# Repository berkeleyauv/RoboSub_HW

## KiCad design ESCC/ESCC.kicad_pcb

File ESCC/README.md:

# ESCC

Based on the STM32F072 NOGGIN, controls a Blue Robotics ESC using PWM over CAN.

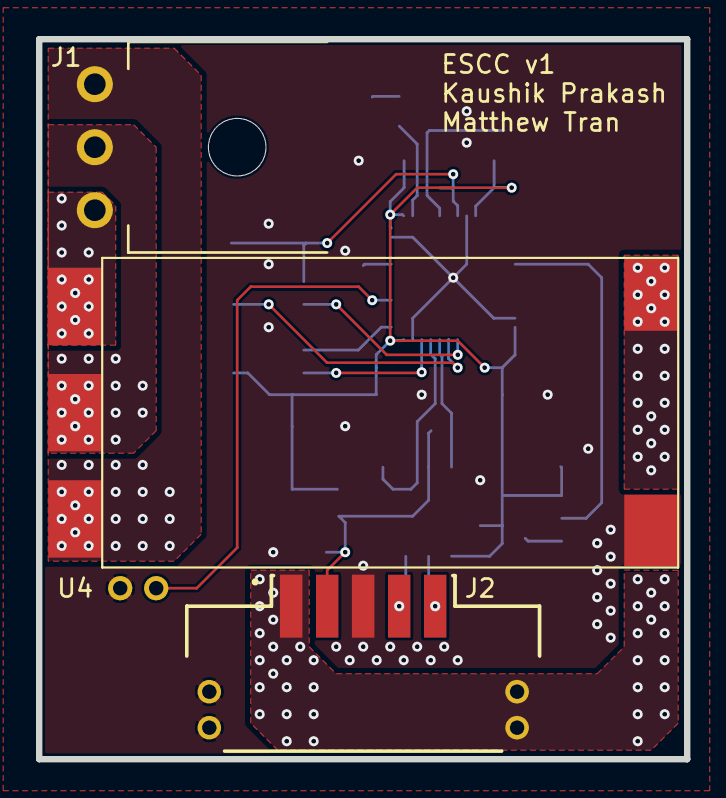
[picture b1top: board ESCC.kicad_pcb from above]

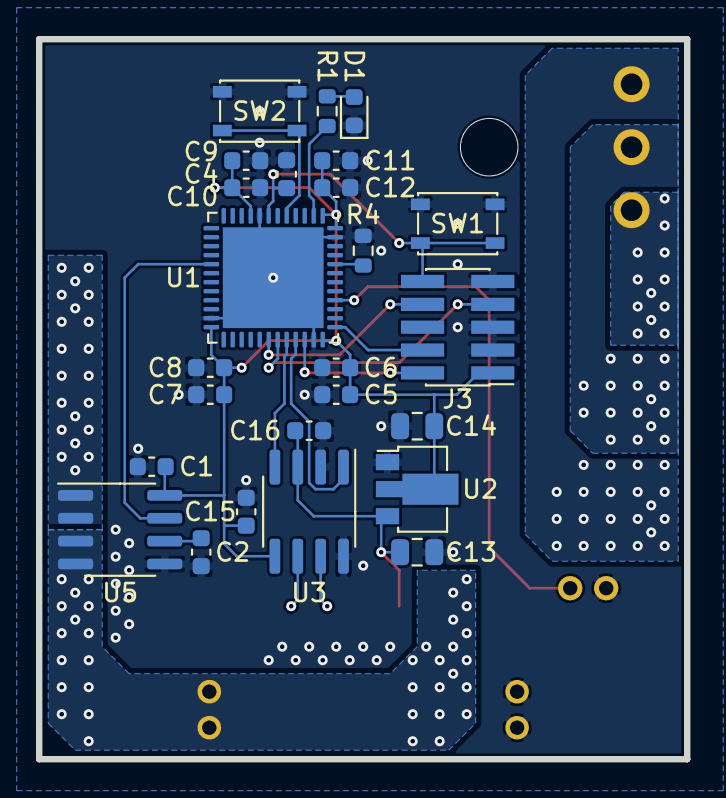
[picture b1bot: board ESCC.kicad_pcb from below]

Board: 2 copper layers, 36.0 x 40.0 mm, 28 parts (25 on the bottom side), 24 nets.

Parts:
C1, C4, C6, C8, C10, C12, C15, C16: 100n; C_0603_1608Metric
C2: DNP; C_0603_1608Metric
C5, C7, C9, C11: 1u; C_0603_1608Metric
C13, C14: 10u; C_0805_2012Metric
D1: LED; LED_0603_1608Metric
J1: Conn_01x03; Molex_UltraFit_RH_3pin
J2: Conn_01x05; Samtec_mPOWER_UMPT_RA_5pin
J3: SWD_UART; PinHeader_2x05_P1.27mm_Vertical_SMD
R1: 150; R_0603_1608Metric
R4: 100k; R_0603_1608Metric
SW1: RST; SW_SPST_PTS810
SW2: DBG; SW_SPST_PTS810
U1: STM32F072CBUx; QFN-48-1EP_7x7mm_P0.5mm_EP5.6x5.6mm
U2: AZ1117-3.3; SOT-89-3
U3: ATA6561; SOIC-8_3.9x4.9mm_P1.27mm
U4: BESC
U5: ACS725xLCTR-30AB; SOIC-8_3.9x4.9mm_P1.27mm

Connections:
+3V3: C1.2, C5.1, C6.1, C7.1, C8.1, C9.1, C10.1, C11.1, C12.1, C14.1, C15.1, J3.1, U1.1, U1.9, U1.24, U1.36, U1.48, U2.2, U3.5, U5.8
+5V: C13.1, C16.1, J2.2, U2.3, U3.3
+12V: J2.1, U5.3, U5.4
/12V_SENSED: U4.4, U5.1, U5.2
/CAN/CANH: J2.4, U3.7
/CAN/CANL: J2.5, U3.6
/CAN_RX: U1.32, U3.4
/CAN_TX: U1.33, U3.1
/CURR_OUT: U1.17, U5.7
/DBG: SW2.1, U1.5
/ESC_SIG: U1.40, U4.2
/LED: R1.2, U1.2
/NOGGIN/PA9(UART_TX): J3.8, U1.30
/NOGGIN/PA10(UART_RX): J3.7, U1.31
/NOGGIN/SWCLK: J3.4, U1.37
/NOGGIN/SWDIO: J3.2, U1.34
/RST: C4.1, J3.10, SW1.1, U1.7
GND: C1.1, C2.1, C4.2, C5.2, C6.2, C7.2, C8.2, C9.2, C10.2, C11.2, C12.2, C13.2, C14.2, C15.2, C16.2, D1.1, J2.3, J3.3, J3.5, J3.9, R4.2, SW1.2, SW2.2, U1.8, U1.23, U1.35, U1.47, U1.49, U2.1, U3.2, U3.8, U4.1, U4.3, U5.5
unnamed: C2.2, U5.6
unnamed: D1.2, R1.1
unnamed: J1.1, U4.7
unnamed: J1.2, U4.6
unnamed: J1.3, U4.5
unnamed: R4.1, U1.44

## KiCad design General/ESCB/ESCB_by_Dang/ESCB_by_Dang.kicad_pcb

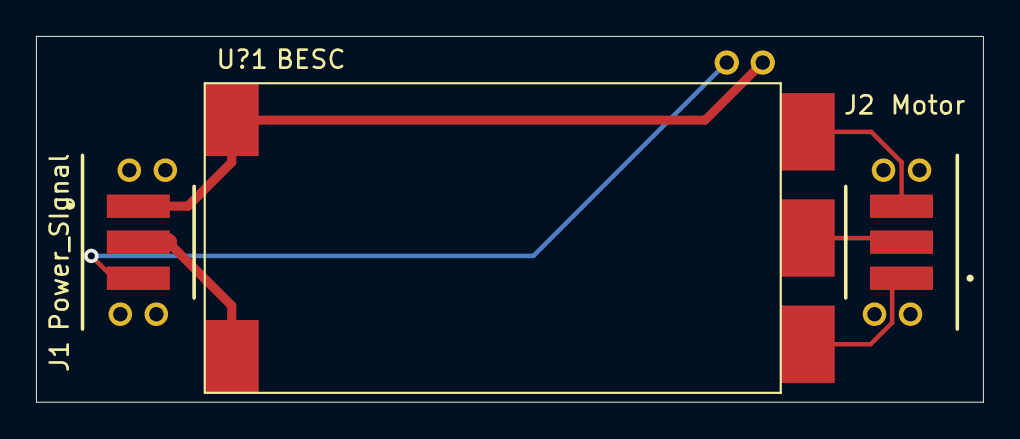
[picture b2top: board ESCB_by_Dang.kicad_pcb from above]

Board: 2 copper layers, 52.6 x 20.3 mm, 3 parts (0 on the bottom side), 6 nets.

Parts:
J1: Power_Signal; Samtec_mPOWER_UMPS_3pin
J2: Motor; Samtec_mPOWER_UMPS_3pin
U?1: BESC

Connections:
GND: J1.1, U?1.1, U?1.3
unnamed: J1.3, U?1.2
unnamed: J2.1, U?1.5
unnamed: J2.2, U?1.6
unnamed: J2.3, U?1.7
VCC: J1.2, U?1.4

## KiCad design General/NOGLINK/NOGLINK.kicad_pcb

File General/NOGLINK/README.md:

# NOGLINK

Carrier for STLINK-V3MODS with CAN transceiver, button, RGB LED, SWD, UART, and stbridge breakout.

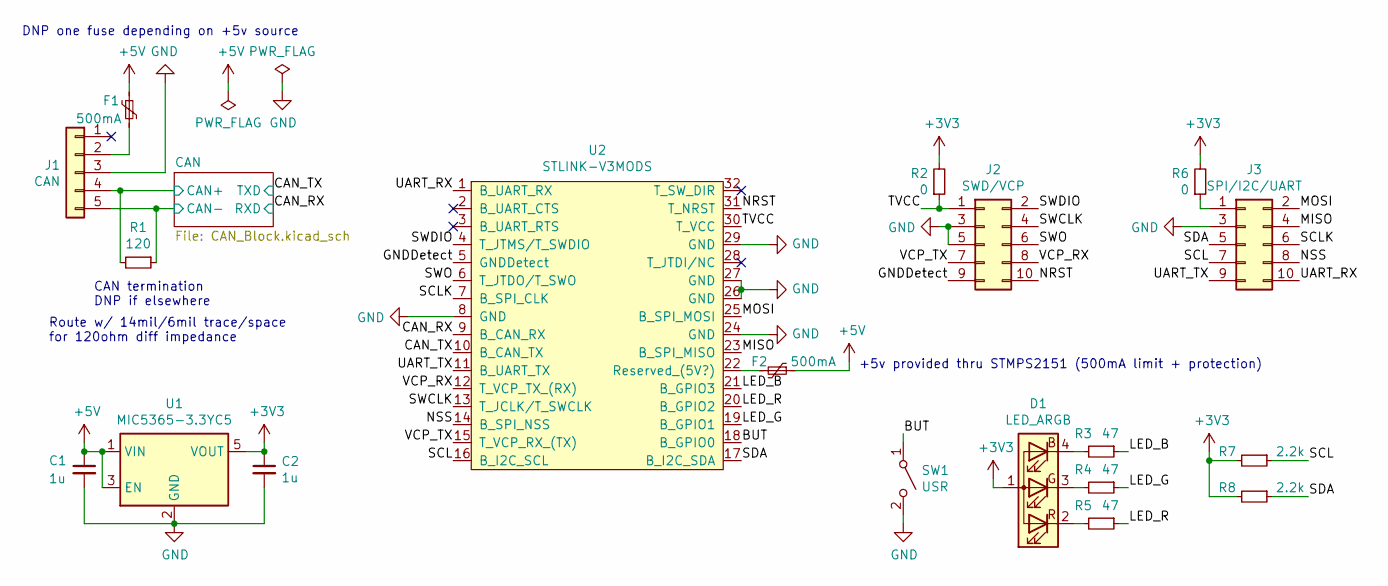
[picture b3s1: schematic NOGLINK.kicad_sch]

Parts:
C1, C2: 1u; C_0603_1608Metric
D1: LED_ARGB; LED_Cree-PLCC4_2x2mm_CW
F1, F2: 500mA; Fuse_1206_3216Metric
J1: CAN; Molex_DuraClik_RH_5pin
J2: SWD/VCP; PinHeader_2x05_P1.27mm_Vertical_SMD
J3: SPI/I2C/UART; PinHeader_2x05_P1.27mm_Vertical_SMD
R1: 120; R_0603_1608Metric
R2, R6: 0; R_0603_1608Metric
R3, R4, R5: 47; R_0603_1608Metric
R7, R8: 2.2k; R_0603_1608Metric
SW1: USR; SW_SPST_PTS810
U1: MIC5365-3.3YC5; SOT-353_SC-70-5
U2: STLINK-V3MODS

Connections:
+3V3: C2.1, D1.1 (A), R2.2, R6.2, R7.2, R8.2, U1.5 (VOUT); also elsewhere on the board
+5V: C1.1, F1.1, F2.1, U1.1 (VIN), U1.3 (EN); also elsewhere on the board
/BUT: SW1.1 (A), U2.18 (B_GPIO0)
/CAN/CAN+: J1.4, R1.2; also elsewhere on the board
/CAN/CAN-: J1.5, R1.1; also elsewhere on the board
/CAN_RX: U2.9 (B_CAN_RX); also elsewhere on the board
/CAN_TX: U2.10 (B_CAN_TX); also elsewhere on the board
/GNDDetect: J2.9, U2.5 (GNDDetect)
/LED_B: R3.1, U2.21 (B_GPIO3)
/LED_G: R4.1, U2.19 (B_GPIO1)
/LED_R: R5.1, U2.20 (B_GPIO2)
/MISO: J3.4, U2.23 (B_SPI_MISO)
/MOSI: J3.2, U2.25 (B_SPI_MOSI)
/NRST: J2.10, U2.31 (T_NRST)
/NSS: J3.8, U2.14 (B_SPI_NSS)
/SCL: J3.7, R7.1, U2.16 (B_I2C_SCL)
/SCLK: J3.6, U2.7 (B_SPI_CLK)
/SDA: J3.5, R8.1, U2.17 (B_I2C_SDA)
/SWCLK: J2.4, U2.13 (T_JCLK/T_SWCLK)
/SWDIO: J2.2, U2.4 (T_JTMS/T_SWDIO)
/SWO: J2.6, U2.6 (T_JTDO/T_SWO)
/TVCC: J2.1, R2.1, U2.30 (T_VCC)
/UART_RX: J3.10, U2.1 (B_UART_RX)
/UART_TX: J3.9, U2.11 (B_UART_TX)
/VCP_RX: J2.8, U2.12 (T_VCP_TX_(RX))
/VCP_TX: J2.7, U2.15 (T_VCP_RX_(TX))
GND: C1.2, C2.2, J1.3, J1.MP, J2.3, J2.5, J3.3, SW1.2 (B), U1.2 (GND), U2.8 (GND), U2.24 (GND), U2.26 (GND), U2.27 (GND), U2.29 (GND); also elsewhere on the board
unnamed: D1.2 (RK), R5.2
unnamed: D1.3 (GK), R4.2
unnamed: D1.4 (BK), R3.2
unnamed: F1.2, J1.2
unnamed: F2.2, U2.22 (Reserved_(5V?))
unnamed: J3.1, R6.1

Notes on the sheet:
+5v provided thru STMPS2151 (500mA limit + protection)
DNP one fuse depending on +5v source
Route w/ 14mil/6mil trace/space for 120ohm diff impedance
CAN termination DNP if elsewhere

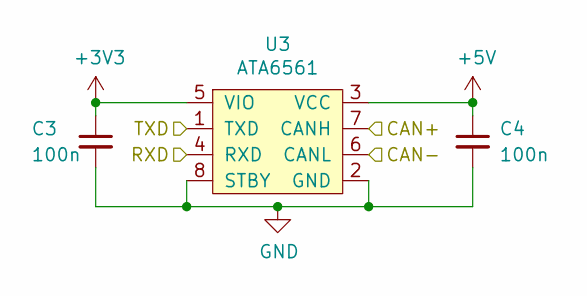
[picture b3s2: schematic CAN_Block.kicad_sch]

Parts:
C3, C4: 100n; C_0603_1608Metric
U3: ATA6561; SOIC-8_3.9x4.9mm_P1.27mm

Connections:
+3V3: C3.1, U3.5 (VIO); also elsewhere on the board
+5V: C4.1, U3.3 (VCC); also elsewhere on the board
/CAN/CAN+: U3.7 (CANH); also elsewhere on the board
/CAN/CAN-: U3.6 (CANL); also elsewhere on the board
/CAN_RX: U3.4 (RXD); also elsewhere on the board
/CAN_TX: U3.1 (TXD); also elsewhere on the board
GND: C3.2, C4.2, U3.2 (GND), U3.8 (STBY); also elsewhere on the board

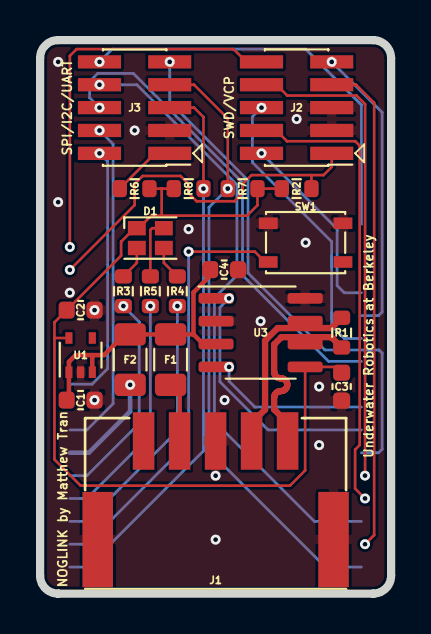
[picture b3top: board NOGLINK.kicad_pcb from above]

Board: 2 copper layers, 19.5 x 30.8 mm, 22 parts (1 on the bottom side), 33 nets.

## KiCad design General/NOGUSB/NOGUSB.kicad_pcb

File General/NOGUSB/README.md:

# NOGUSB

Board for testing various capabilities of the STM32G0B1 including USB-C PD, USB, bootloaders, and FDCAN. Intended as potential replacement for NOGLINK.

If using the bootloader to program, make sure to unset the nBOOT_SEL before first flash or you will lose access to the bootloader.

## Revisions

### v1.1

- Added connections for DBCC pins, fixing no power on startup
- Rerouted UART pins to a different pair

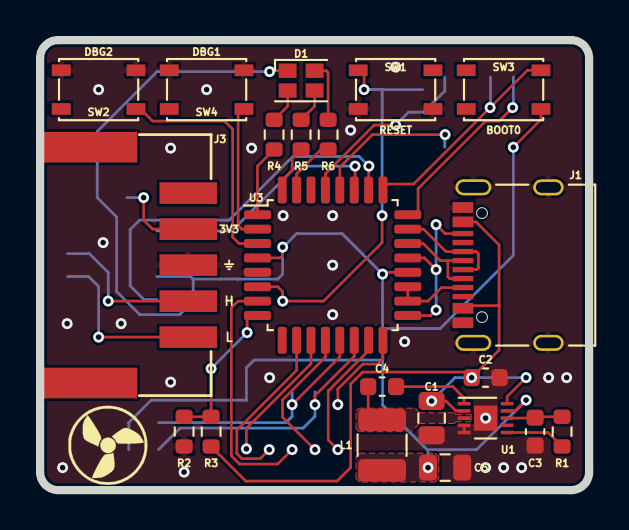
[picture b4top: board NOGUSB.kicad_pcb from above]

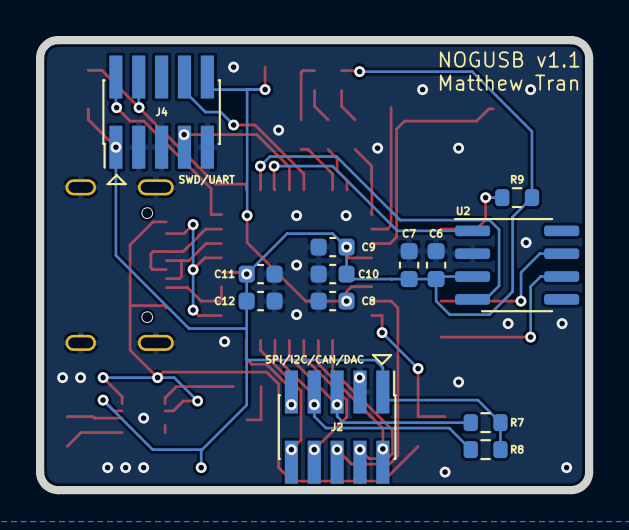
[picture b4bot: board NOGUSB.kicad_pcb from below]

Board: 2 copper layers, 30.5 x 25.0 mm, 35 parts (13 on the bottom side), 38 nets.

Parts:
C1, C5: 22u; C_0805_2012Metric
C2, C4, C6, C8, C9, C11: 100n; C_0603_1608Metric
C3: 1u; C_0603_1608Metric
C7, C10, C12: 4.7u; C_0603_1608Metric
D1: LED_ARGB; LED_Cree-PLCC4_2x2mm_CW
H1: Logo; auv_logo
J1: USB4105-GF-A; USB_C_Receptacle_Palconn_UTC16-G
J2: SPI/I2C/CAN/DAC; PinHeader_2x05_P1.27mm_Vertical_SMD
J3: CAN; Molex_DuraClik_RH_5pin
J4: SWD_UART; PinHeader_2x05_P1.27mm_Vertical_SMD
L1: 10u; L_1210_3225Metric
R1, R2: 100k; R_0603_1608Metric
R3: 10k; R_0603_1608Metric
R4, R5, R6: 47; R_0603_1608Metric
R7, R8: 2k2; R_0603_1608Metric
R9: 0; R_0603_1608Metric
SW1: RST; SW_SPST_PTS810
SW2: DBG2; SW_SPST_PTS810
SW3: BOOT0; SW_SPST_PTS810
SW4: DBG1; SW_SPST_PTS810
U1: MAX77596ETBB+
U2: TCAN330G; SOIC-8_3.9x4.9mm_P1.27mm
U3: STM32G0B1KxTxN; LQFP-32_7x7mm_P0.8mm

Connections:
+3V3: C5.1, C6.1, C7.1, C9.1, C10.1, C11.1, C12.1, D1.1, J2.1, J4.1, L1.2, R7.2, R8.2, R9.1, SW3.2, U1.9, U2.3, U3.4, U3.20
/BOOT0: J4.4, SW3.1, U3.25
/CAN2_RX: J2.10, U3.15
/CAN2_TX: J2.9, U3.16
/CAN/CANH: J3.4, U2.7
/CAN/CANL: J3.5, U2.6
/CAN_RX: U2.4, U3.26
/CAN_TX: U2.1, U3.27
/DAC: J2.8, U3.12
/DBG1: SW4.1, U3.2
/DBG2: SW2.1, U3.3
/I2C_SCL: J2.7, R8.1, U3.14
/I2C_SDA: J2.5, R7.1, U3.13
/LED_B: R4.1, U3.1
/LED_G: R5.1, U3.32
/LED_R: R6.1, U3.31
/NOGGIN/PA13(SWDIO): J4.2, U3.24
/NOGGIN/PD2: J4.7, U3.28
/NOGGIN/PD3: J4.8, U3.29
/RST: C8.1, J4.10, SW1.1, U3.6
/SPI_CLK: J2.6, U3.7
/SPI_MISO: J2.4, U3.10
/SPI_MOSI: J2.2, U3.11
/USB_CC1: J1.A5, U3.18, U3.19
/USB_CC2: J1.B5, U3.17, U3.21
/USB_DM: J1.A7, J1.B7, U3.22
/USB_DP: J1.A6, J1.B6, U3.23
/VBUS_MON: R2.2, R3.1, U3.8
GND: C1.2, C2.2, C3.2, C5.2, C6.2, C7.2, C8.2, C9.2, C10.2, C11.2, C12.2, J1.A1, J1.A12, J1.B1, J1.B12, J1.S1, J2.3, J3.3, J4.3, J4.5, J4.9, R3.2, SW1.2, SW2.2, SW4.2, U1.4, U1.5, U1.11, U2.2, U3.5
unnamed: C3.1, R1.1, U1.8
unnamed: C4.1, L1.1, U1.3
unnamed: C4.2, U1.1
unnamed: D1.2, R6.2
unnamed: D1.3, R5.2
unnamed: D1.4, R4.2
unnamed: J3.2, R9.2
unnamed: R1.2, U1.6
VBUS: C1.1, C2.1, J1.A4, J1.A9, J1.B4, J1.B9, R2.1, U1.2, U1.10

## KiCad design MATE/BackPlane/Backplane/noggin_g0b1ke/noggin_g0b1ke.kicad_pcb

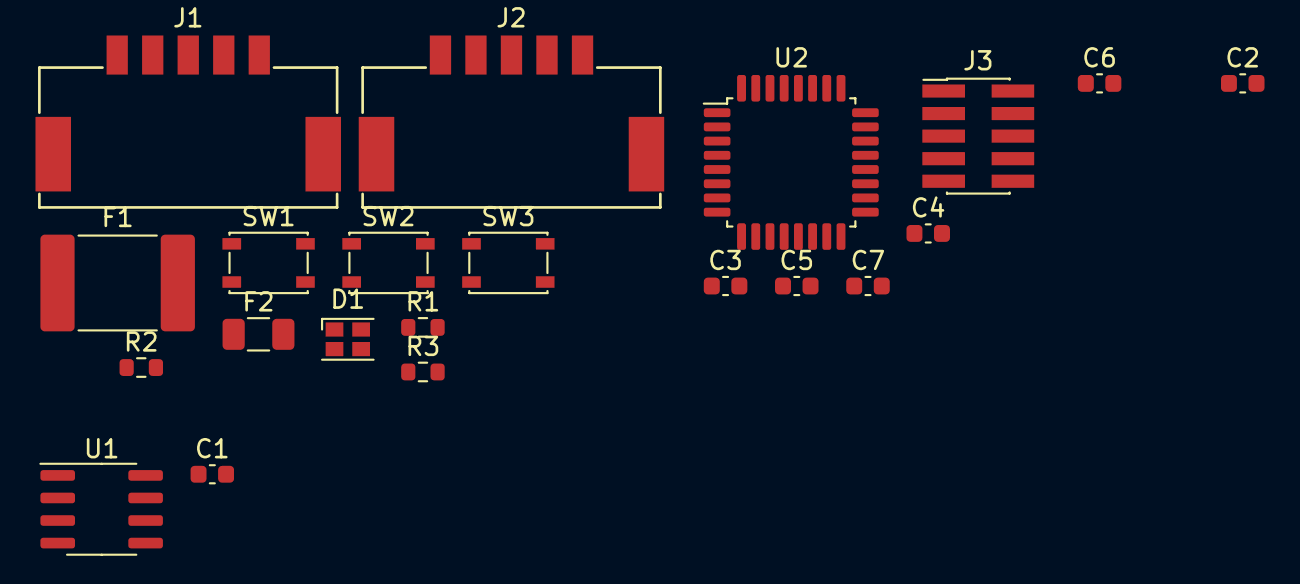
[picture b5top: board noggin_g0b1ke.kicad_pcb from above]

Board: 2 copper layers, 21 parts (0 on the bottom side), 21 nets, no tracks yet.

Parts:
C1, C3, C4, C6: 100n; C_0603_1608Metric
C2, C5, C7: 4.7u; C_0603_1608Metric
D1: LED_ARGB; LED_Cree-PLCC4_2x2mm_CW
F1: 5A; Fuse_2920_7451Metric
F2: 1A; Fuse_1206_3216Metric
J1, J2: CAN; Molex_DuraClik_Vert_5pin
J3: SWD_UART; PinHeader_2x05_P1.27mm_Vertical_SMD
R1, R2, R3: 47; R_0603_1608Metric
SW1: DBG2; SW_SPST_PTS810
SW2: DBG1; SW_SPST_PTS810
SW3: RST; SW_SPST_PTS810
U1: TCAN330G; SOIC-8_3.9x4.9mm_P1.27mm
U2: STM32G0B1KxTxN; LQFP-32_7x7mm_P0.8mm

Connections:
+3V3: C1.1, C2.1, C4.1, C5.1, C6.1, C7.1, D1.1, F2.1, J3.1, U1.3, U2.4, U2.20
/CAN/CANH: J1.4, J2.4, U1.7
/CAN/CANL: J1.5, J2.5, U1.6
/CAN_RX: U1.4, U2.26
/CAN_TX: U1.1, U2.27
/DBG1: SW2.1, U2.2
/DBG2: SW1.1, U2.3
/LED_B: R1.1, U2.1
/LED_G: R2.1, U2.32
/LED_R: R3.1, U2.31
/NOGGIN/PA9(TX): J3.8, U2.19
/NOGGIN/PA10(RX): J3.7, U2.21
/NOGGIN/PA13(SWDIO): J3.2, U2.24
/NOGGIN/PA14-BOOT0(SWCLK): J3.4, U2.25
/RST: C3.1, J3.10, SW3.1, U2.6
GND: C1.2, C2.2, C3.2, C4.2, C5.2, C6.2, C7.2, J1.3, J2.3, J3.3, J3.5, J3.9, SW1.2, SW2.2, SW3.2, U1.2, U2.5
unnamed: D1.2, R3.2
unnamed: D1.3, R2.2
unnamed: D1.4, R1.2
unnamed: F1.2, J1.1, J2.1
unnamed: F2.2, J1.2, J2.2

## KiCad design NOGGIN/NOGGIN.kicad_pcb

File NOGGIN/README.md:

# NOGGIN

Based on the STM32F072 (or alternately the STM32F091), NOGGIN is a general purpose board containing current/voltage sense, brushed motor driver, CAN, I2C/UART/DAC/ADC connectors, debug switches, RGB LED, and GPIO breakout.

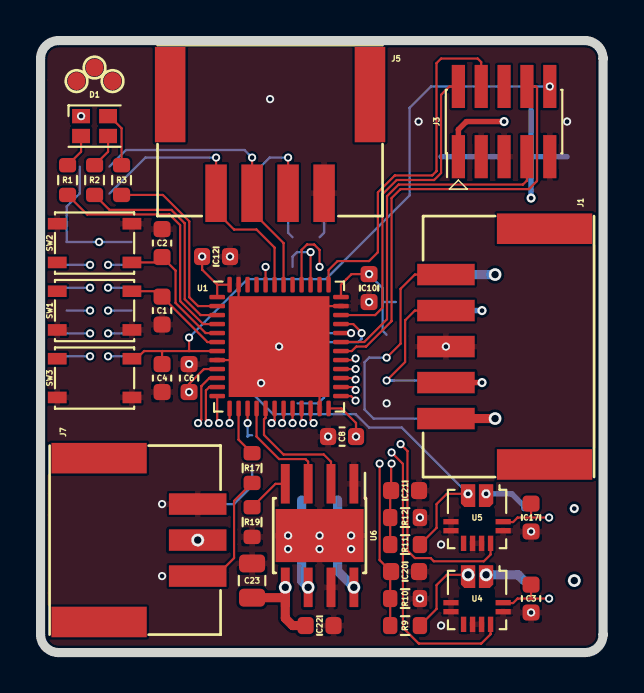
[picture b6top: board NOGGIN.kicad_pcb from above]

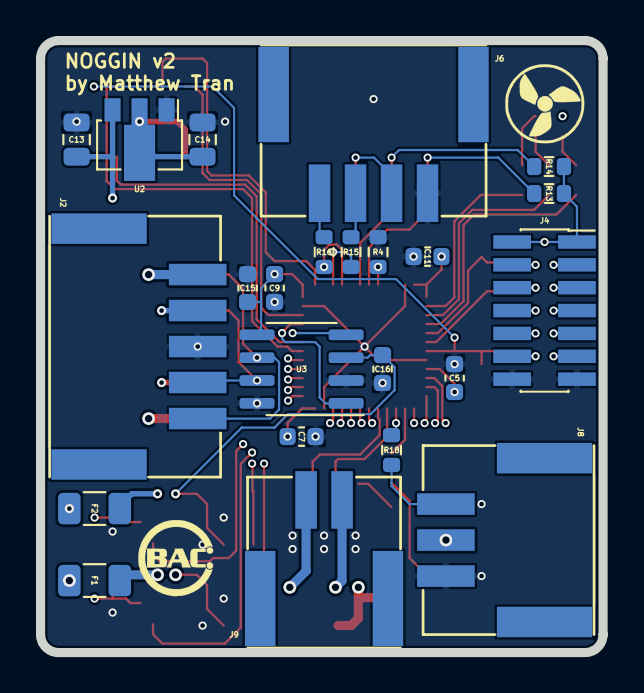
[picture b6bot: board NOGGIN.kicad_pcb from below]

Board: 4 copper layers, 31.2 x 34.0 mm, 58 parts (23 on the bottom side), 55 nets.

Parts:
 : version_dots
C1, C2, C3, C4, C6, C8, C10, C12, C15, C16, C17, C20, C21, C22: 100n; C_0603_1608Metric
C5, C7, C9, C11: 1u; C_0603_1608Metric
C13, C14, C23: 10u; C_0805_2012Metric
D1: LED_ARGB; LED_Cree-PLCC4_2x2mm_CW
F1: 5A; Fuse_1206_3216Metric
F2: 1A; Fuse_1206_3216Metric
J1, J2: CAN; Molex_DuraClik_RH_5pin
J3: SWD_UART; PinHeader_2x05_P1.27mm_Vertical_SMD
J4: Extra; PinSocket_2x07_P1.27mm_Vertical_SMD
J5: I2C; Molex_DuraClik_RH_4pin
J6: UART; Molex_DuraClik_RH_4pin
J7: DAC1; Molex_DuraClik_RH_3pin
J8: DAC2; Molex_DuraClik_RH_3pin
J9: MOTOR; Molex_DuraClik_RH_2pin
R1, R2, R3: 47; R_0603_1608Metric
R4, R9: 100k; R_0603_1608Metric
R10, R12: 10k; R_0603_1608Metric
R11: 47k; R_0603_1608Metric
R13, R14: 2.2k; R_0603_1608Metric
R15, R16, R17, R18: 22; R_0603_1608Metric
R19: 22k; R_0603_1608Metric
SW1: DBG2; SW_SPST_PTS810
SW2: DBG1; SW_SPST_PTS810
SW3: RST; SW_SPST_PTS810
U1: STM32F072CBUx; QFN-48-1EP_7x7mm_P0.5mm_EP5.6x5.6mm
U2: AZ1117-3.3; SOT-89-3
U3: ATA6561; SOIC-8_3.9x4.9mm_P1.27mm
U4, U5: ACS70331; Allegro_QFN-12-10-1EP_3x3mm_P0.5mm
U6: DRV8871DDA; Texas_HTSOP-8-1EP_3.9x4.9mm_P1.27mm_EP2.95x4.9mm_Mask2.4x3.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

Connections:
+3V3: C3.1, C5.1, C6.1, C7.1, C8.1, C9.1, C10.1, C11.1, C12.1, C14.1, C15.1, C17.1, D1.1, J3.1, J4.1, J4.2, J5.2, J6.2, R13.1, R14.1, U1.1, U1.9, U1.24, U1.36, U1.48, U2.2, U3.5, U4.10, U5.10
+5V: C13.1, C16.1, R11.1, U2.3, U3.3, U5.2
+12V: C22.1, C23.1, J7.2, J8.2, R9.1, U4.2, U6.5
/5v_Isens: U1.13, U5.8
/5v_Sens+: F2.1, U5.1
/5v_Vsens: C21.2, R11.2, R12.1, U1.11
/12v_Isens: U1.12, U4.8
/12v_Sens+: F1.1, U4.1
/12v_Vsens: C20.2, R9.2, R10.1, U1.10
/CAN/CANH: J1.4, J2.4, U3.7
/CAN/CANL: J1.5, J2.5, U3.6
/CAN_RX: U1.32, U3.4
/CAN_TX: U1.33, U3.1
/DAC1: R17.2, U1.14
/DAC2: R18.2, U1.15
/DBG1: C2.1, SW2.1, U1.5
/DBG2: C1.1, SW1.1, U1.6
/LED_B: R1.1, U1.4
/LED_G: R2.1, U1.3
/LED_R: R3.1, U1.2
/NOGGIN/PA9(UART_TX): J3.8, U1.30
/NOGGIN/PA10(UART_RX): J3.7, U1.31
/NOGGIN/SWCLK: J3.4, U1.37
/NOGGIN/SWDIO: J3.2, U1.34
/PA8: J4.3, U1.29
/PB0: J4.12, U1.18
/PB1: J4.11, U1.19
/PB2: J4.10, U1.20
/PB10: J4.9, U1.21
/PB11: J4.8, U1.22
/PB12: J4.7, U1.25
/PB13: J4.6, U1.26
/PB14: J4.5, U1.27
/PB15: J4.4, U1.28
/RST: C4.1, J3.10, SW3.1, U1.7
/RX: R16.2, U1.40
/SCL: J5.3, R14.2, U1.42
/SDA: J5.4, R13.2, U1.43
/TX: R15.2, U1.39
/motor_in1: U1.16, U6.3
/motor_in2: U1.17, U6.2
GND: C1.2, C2.2, C3.2, C4.2, C5.2, C6.2, C7.2, C8.2, C9.2, C10.2, C11.2, C12.2, C13.2, C14.2, C15.2, C16.2, C17.2, C20.1, C21.1, C22.2, C23.2, J1.3, J2.3, J3.3, J3.5, J3.9, J4.13, J4.14, J5.1, J6.1, J7.1, J8.1, R4.2, R10.2, R12.2, R19.2, SW1.2, SW2.2, SW3.2, U1.8, U1.23, U1.35, U1.47, U1.49, U2.1, U3.2, U3.8, U4.3, U4.4, U4.6, U4.7, U4.9, U5.3, U5.4, U5.6, U5.7, U5.9, U6.1, U6.7, U6.9
unnamed: D1.2, R3.2
unnamed: D1.3, R2.2
unnamed: D1.4, R1.2
unnamed: F1.2, J1.1, J2.1
unnamed: F2.2, J1.2, J2.2
unnamed: J6.3, R15.1
unnamed: J6.4, R16.1
unnamed: J7.3, R17.1
unnamed: J8.3, R18.1
unnamed: J9.1, U6.8
unnamed: J9.2, U6.6
unnamed: R4.1, U1.44
unnamed: R19.1, U6.4

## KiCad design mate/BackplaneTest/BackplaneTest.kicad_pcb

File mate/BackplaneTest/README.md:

# BackplaneTest

Tests the ESCC and PCC along with a Molex Super Sabre for power.

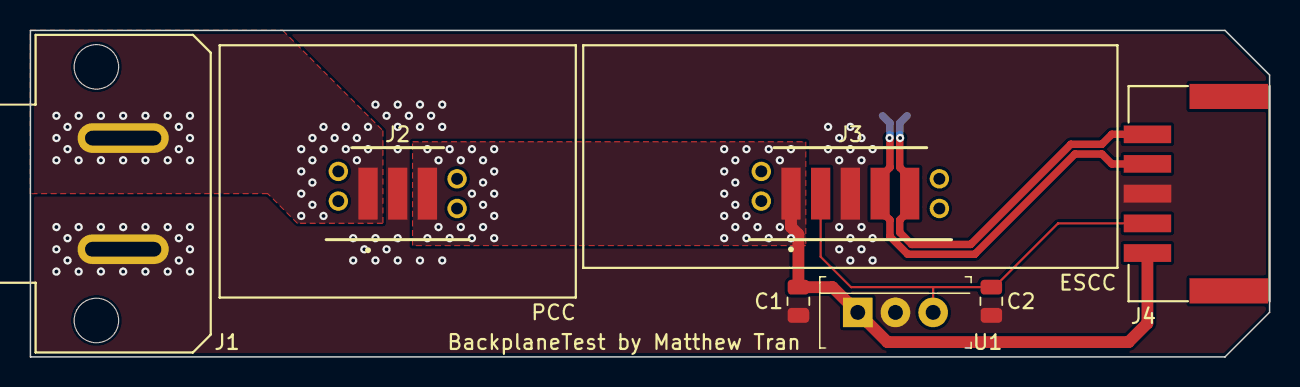
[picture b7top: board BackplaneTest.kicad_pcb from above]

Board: 2 copper layers, 83.5 x 22.0 mm, 8 parts (1 on the bottom side), 6 nets.

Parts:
C1, C2: 10u; C_0805_2012Metric
J1: Power; Molex_SuperSabre_Vert_2pin
J2: PCC; Samtec_mPOWER_UMPS_3pin
J3: ESCC; Samtec_mPOWER_UMPS_5pin
J4: CAN; Molex_DuraClik_RH_5pin
R1: 120; R_0603_1608Metric
U1: L7805CV; TO-220-3

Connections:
+5V: C2.1, J3.2, J4.2, U1.3
+12V: C1.2, J2.3, J3.1, J4.1, U1.1
+48V: J1.2, J2.1
/CAN+: J3.4, J4.4, R1.2
/CAN-: J3.5, J4.5, R1.1
GND: C1.1, C2.2, J1.1, J2.2, J3.3, J4.3, U1.2
